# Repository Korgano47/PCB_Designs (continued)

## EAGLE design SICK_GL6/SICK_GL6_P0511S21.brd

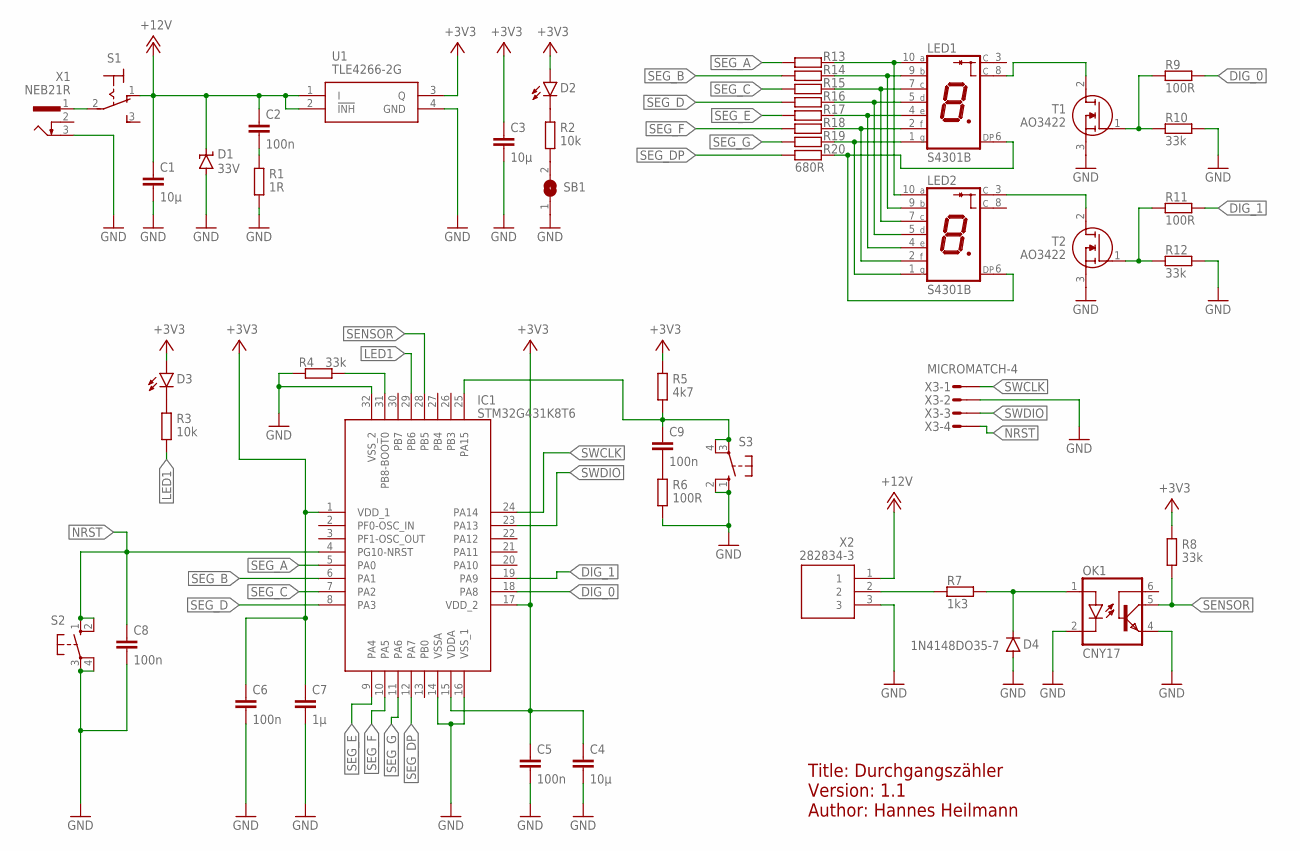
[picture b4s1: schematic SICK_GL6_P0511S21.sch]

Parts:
C1, C3, C4: 10µ; C1206K
C2, C5, C6, C8, C9: 100n; C0805K
C7: 1µ; C1206K
D1: 33V; SMBJ
D2, D3: LEDSML0805; SML0805
D4: 1N4148DO35-7; DO35-7
IC1: STM32G431K8T6; QFP80P900X900X160-32N
LED1, LED2: S4301B
OK1: CNY17; DIL06
R1: 1R; R0805
R2, R3: 10k; R0805
R4, R8, R10, R12: 33k; R0805
R5: 4k7; R0805
R6, R9, R11: 100R; R0805
R7: 1k3; R0805
R13, R14, R15, R16, R17, R18, R19, R20: 680R; R0805
S1: M9040P
S2, S3: 10-XX; B3F-10XX
SB1: SJ
T1, T2: AO3422; SOT95P237X112-3N
U1: TLE4266-2G; SOT230P700X170-4N
X1: NEB21R
X2: 282834-3; SHDR3W100P0X254_1X3_808X650X10
X3: MICROMATCH-4

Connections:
+3V3: C3.1, C4.1, C5.1, C6.1, C7.1, D2.A, D3.A, IC1.1 (VDD_1), IC1.15 (VDDA), IC1.17 (VDD_2), R5.2, R8.2, U1.3 (Q)
+12V: C1.1, C2.1, D1.C, S1.1 (O), U1.1 (I), U1.2 (!INH), X2.1
DIG_0: IC1.18 (PA8), R9.1
DIG_1: IC1.19 (PA9), R11.1
GND: C1.2, C3.2, C4.2, C5.2, C6.2, C7.2, C8.2, D1.A, D4.A, IC1.14 (VSSA), IC1.16 (VSS_1), IC1.32 (VSS_2), OK1.2 (C), OK1.4 (EMI), R1.1, R4.2, R6.1, R10.1, R12.1, S2.3, S2.4 (P1), S3.1 (S), S3.2 (S1), SB1.1, T1.3 (S), T2.3 (S), U1.4 (GND), X1.3, X2.3, X3.2
LED1: IC1.29 (PB6), R3.1
unnamed: S1.2, X1.1
unnamed: C2.2, R1.2
unnamed: D4.C, OK1.1 (A), R7.1
unnamed: LED2.3 (C), T2.2 (D)
unnamed: D2.C, R2.2
unnamed: R7.2, X2.2
unnamed: C9.1, IC1.25 (PA15), R5.1, S3.3, S3.4 (P1)
unnamed: C9.2, R6.2
unnamed: LED1.8 (C), T1.2 (D)
unnamed: IC1.31 (PB8-BOOT0), R4.1
unnamed: R2.1, SB1.2
unnamed: R11.2, R12.2, T2.1 (G)
unnamed: R9.2, R10.2, T1.1 (G)
unnamed: D3.C, R3.2
NRST: C8.1, IC1.4 (PG10-NRST), S2.1 (S), S2.2 (S1), X3.4
SEG_A: IC1.5 (PA0), R13.2
SEG_B: IC1.6 (PA1), R14.2
SEG_C: IC1.7 (PA2), R15.2
SEG_D: IC1.8 (PA3), R16.2
SEG_DP: IC1.12 (PA7), R20.2
SEG_E: IC1.9 (PA4), R17.2
SEG_F: IC1.10 (PA5), R18.2
SEG_G: IC1.11 (PA6), R19.2
SENSOR: IC1.28 (PB5), OK1.5 (COL), R8.1
SWCLK: IC1.24 (PA14), X3.1
SWDIO: IC1.23 (PA13), X3.3
S_A: LED1.10 (A), LED2.10 (A), R13.1
S_B: LED1.9 (B), LED2.9 (B), R14.1
S_C: LED1.7 (C), LED2.7 (C), R15.1
S_D: LED1.5 (D), LED2.5 (D), R16.1
S_DP: LED1.6 (DP), LED2.6 (DP), R20.1
S_E: LED1.4 (E), LED2.4 (E), R17.1
S_F: LED1.2 (F), LED2.2 (F), R18.1
S_G: LED1.1 (G), LED2.1 (G), R19.1

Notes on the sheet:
Title: Durchgangszähler Version: 1.1 Author: Hannes Heilmann

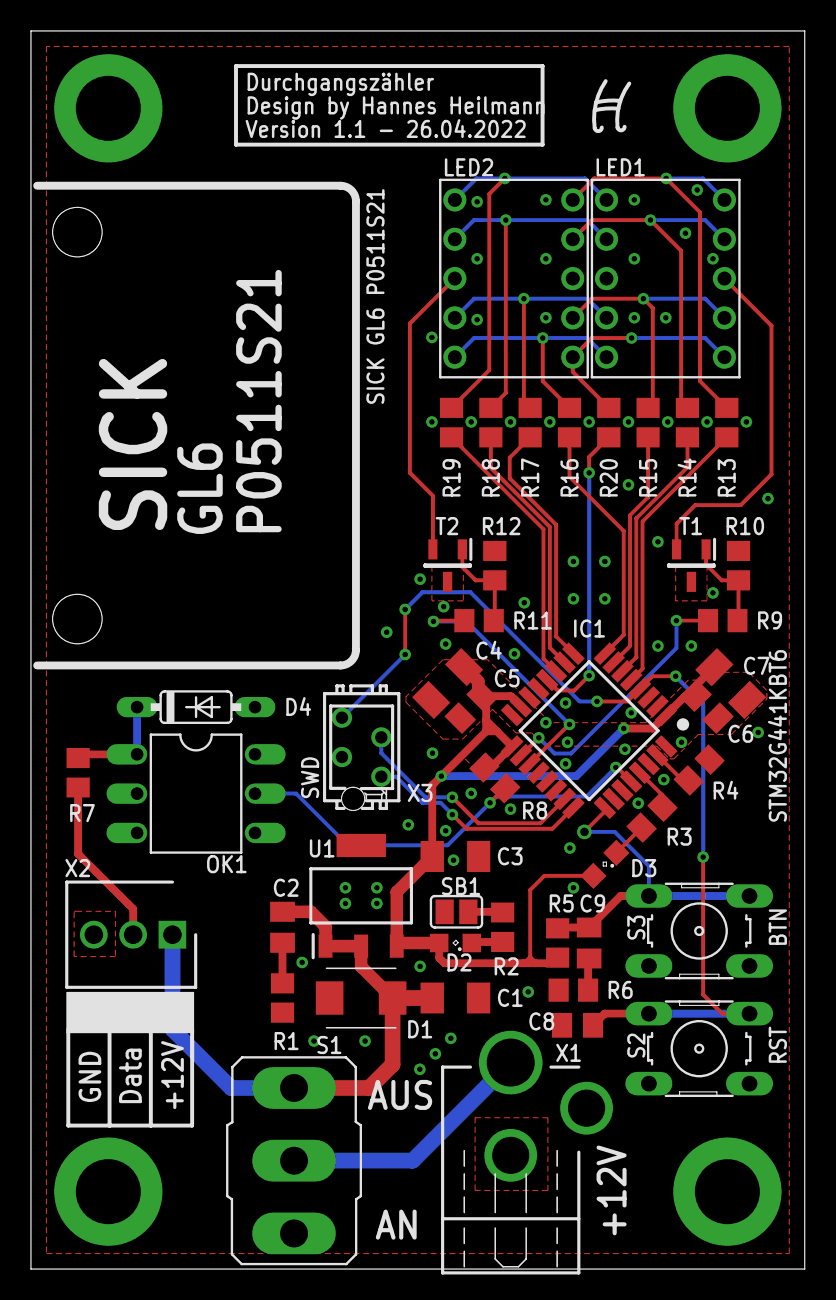
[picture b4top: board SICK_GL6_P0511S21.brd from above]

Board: 2 copper layers, 50.0 x 80.0 mm, 47 parts (0 on the bottom side), 40 nets.

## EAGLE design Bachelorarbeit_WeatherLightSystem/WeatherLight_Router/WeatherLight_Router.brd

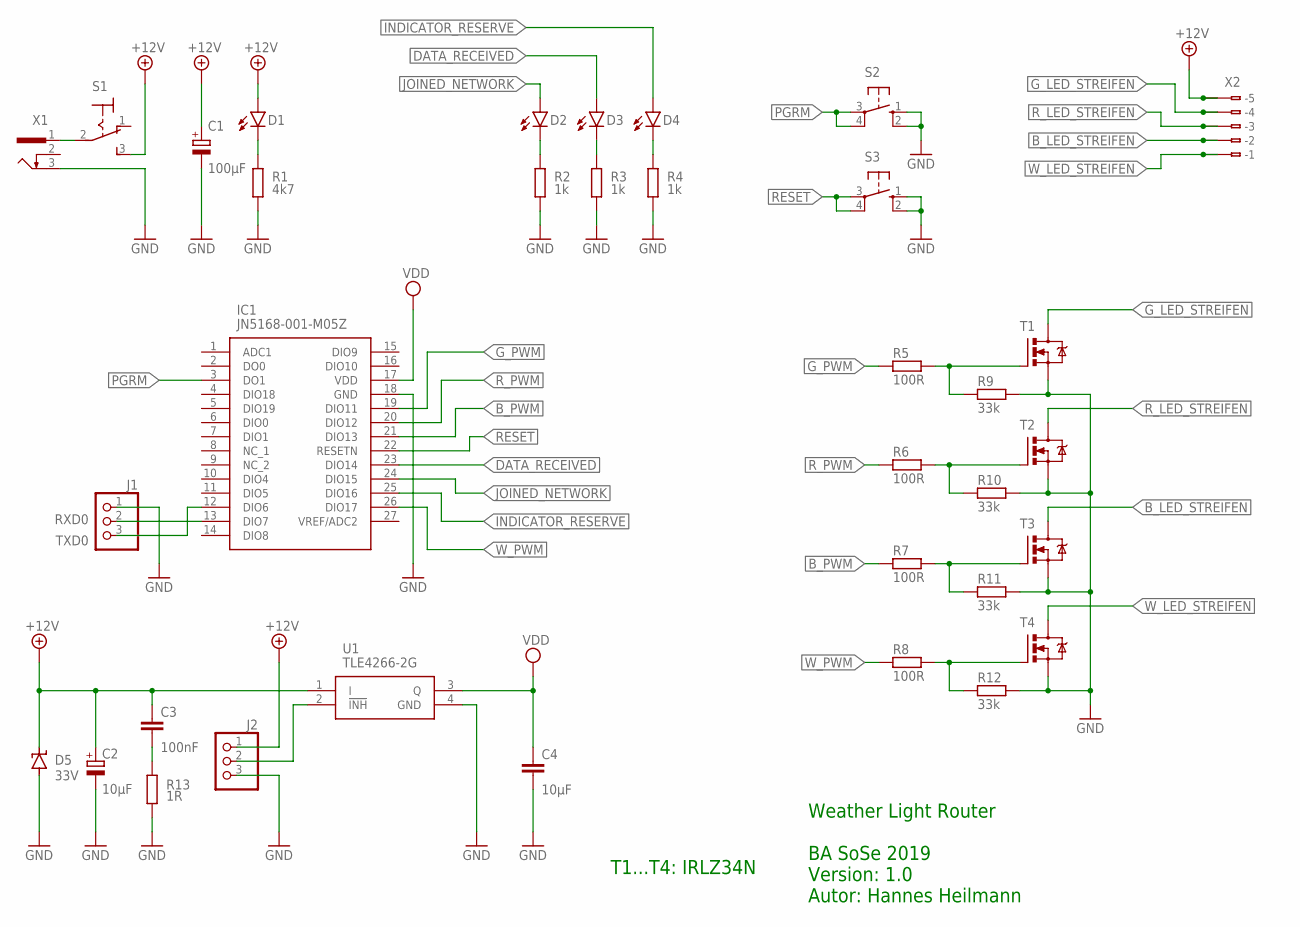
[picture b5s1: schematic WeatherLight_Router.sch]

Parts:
C1: 100µF; PANASONIC_D
C2: 10µF; PANASONIC_B
C3: 100nF; C1206
C4: 10µF; C1206K
D1, D2, D3, D4: LEDCHIPLED_1206; CHIPLED_1206
D5: 33V; SMBJ
IC1: JN5168-001-M05Z; JN5168001M05Z
J1, J2: PINHD-1X3; 1X03
R1: 4k7; R1206
R2, R3, R4: 1k; R1206
R5, R6, R7, R8: 100R; R1206
R9, R10, R11, R12: 33k; R1206
R13: 1R; R1206
S1: M9040P
S2, S3: 10-XX; B3F-10XX
T1, T2, T3, T4: IRLZ44Z; TO220BH
U1: TLE4266-2G; SOT230P700X170-4N
X1: NEB21R
X2: 233-505

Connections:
+12V: C1.+, C2.+, C3.1, D1.A, D5.C, J2.1, S1.3 (S), U1.1 (I), X2.A5 (-5), X2.B5 (B-5)
B_LED_STREIFEN: T3.D, X2.A2 (-2), X2.B2 (B-2)
B_PWM: IC1.21 (DIO13), R7.1
DATA_RECEIVED: D3.A, IC1.23 (DIO14)
GND: C1.-, C2.-, C4.2, D5.A, IC1.18 (GND), J1.1, J2.3, R1.1, R2.1, R3.1, R4.1, R9.2, R10.2, R11.2, R12.2, R13.1, S2.1 (S), S2.2 (S1), S3.1 (S), S3.2 (S1), T1.S, T2.S, T3.S, T4.S, U1.4 (GND), X1.3
G_LED_STREIFEN: T1.D, X2.A4 (-4), X2.B4 (B-4)
G_PWM: IC1.19 (DIO11), R5.1
INDICATOR_RESERVE: D4.A, IC1.25 (DIO16)
JOINED_NETWORK: D2.A, IC1.24 (DIO15)
unnamed: J2.2, U1.2 (!INH)
unnamed: S1.2, X1.1
unnamed: D1.C, R1.2
unnamed: D4.C, R4.2
unnamed: R7.2, R11.1, T3.G
unnamed: R8.2, R12.1, T4.G
unnamed: R6.2, R10.1, T2.G
unnamed: R5.2, R9.1, T1.G
unnamed: D3.C, R3.2
unnamed: D2.C, R2.2
unnamed: C3.2, R13.2
PGRM: IC1.3 (DO1), S2.3, S2.4 (P1)
RESET: IC1.22 (RESETN), S3.3, S3.4 (P1)
RXD0: IC1.13 (DIO7), J1.2
R_LED_STREIFEN: T2.D, X2.A3 (-3), X2.B3 (B-3)
R_PWM: IC1.20 (DIO12), R6.1
TXD0: IC1.12 (DIO6), J1.3
VDD: C4.1, IC1.17 (VDD), U1.3 (Q)
W_LED_STREIFEN: T4.D, X2.A1 (-1), X2.B1 (B-1)
W_PWM: IC1.26 (DIO17), R8.1

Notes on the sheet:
Weather Light Router BA SoSe 2019 Version: 1.0 Autor: Hannes Heilmann
T1...T4: IRLZ34N

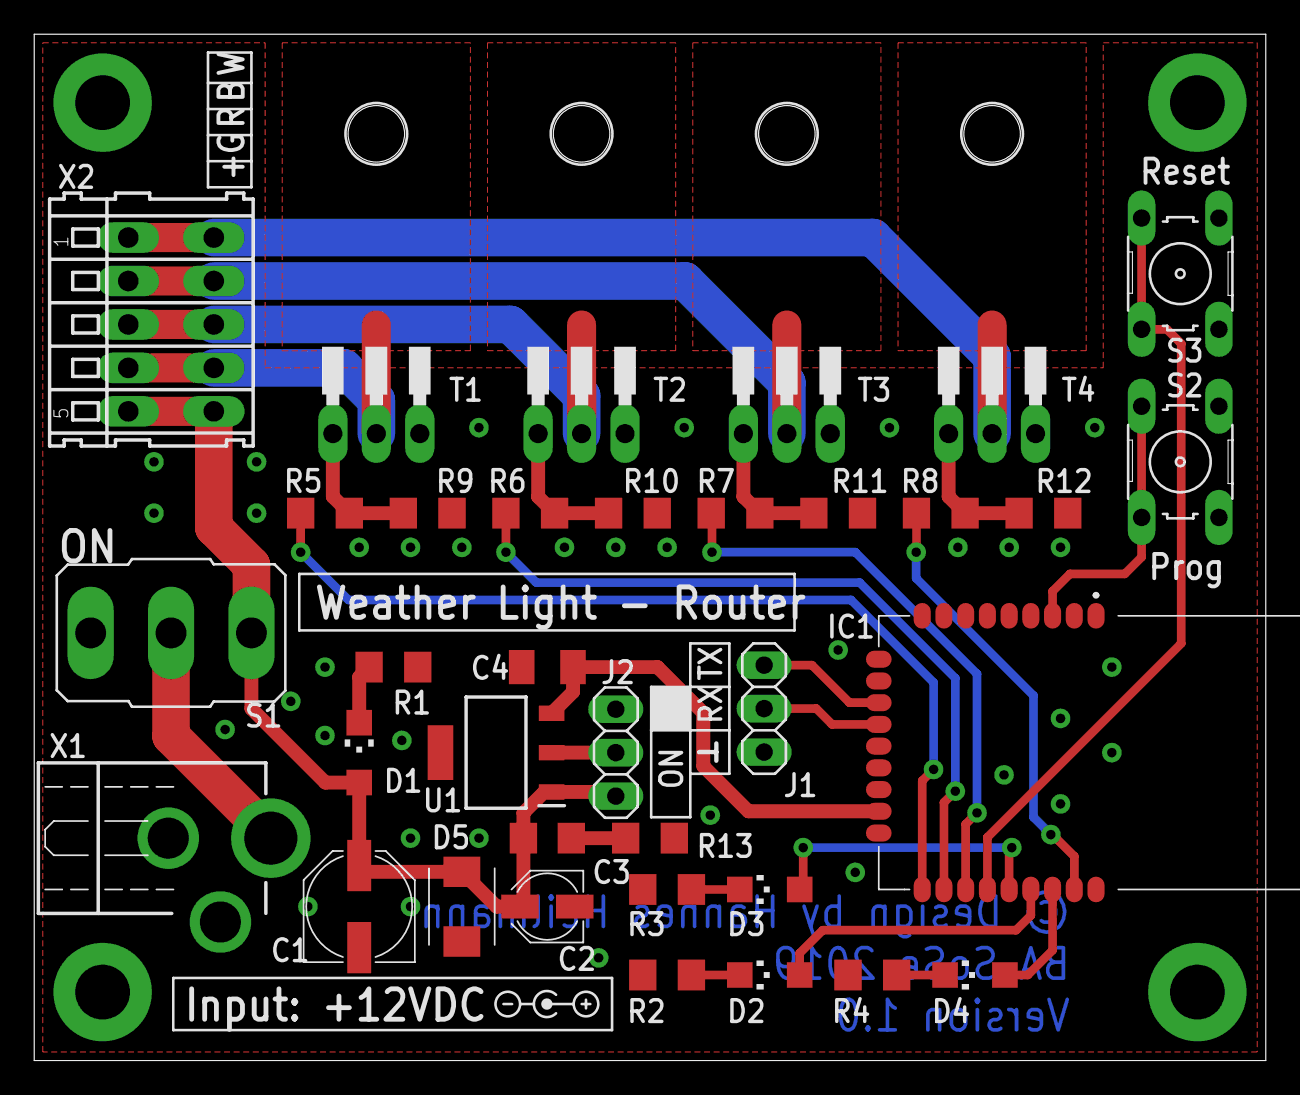
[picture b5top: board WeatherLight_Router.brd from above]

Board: 2 copper layers, 72.0 x 60.0 mm, 35 parts (0 on the bottom side), 29 nets.

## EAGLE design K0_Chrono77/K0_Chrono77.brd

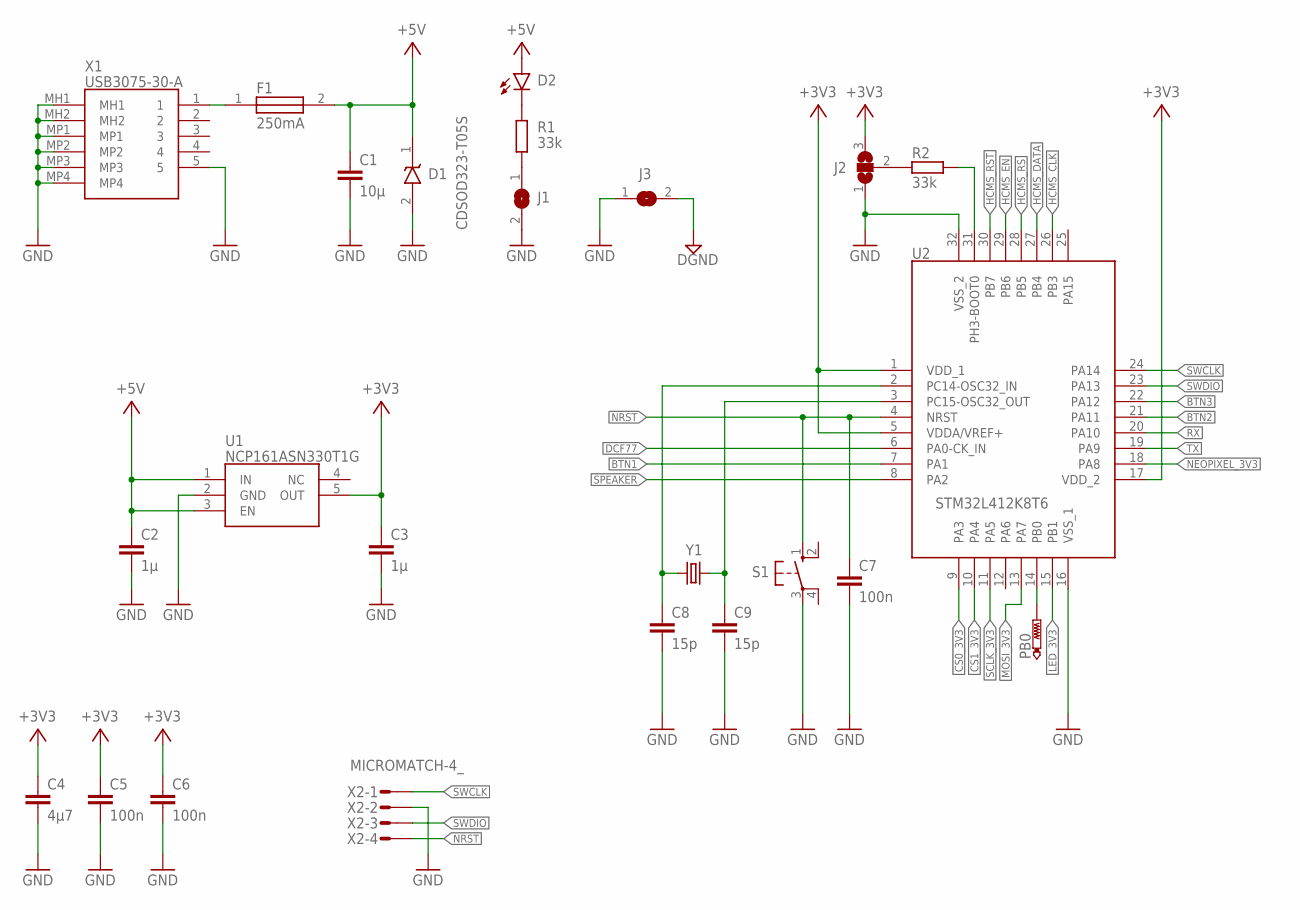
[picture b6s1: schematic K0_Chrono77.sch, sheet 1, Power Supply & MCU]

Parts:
C1: 10μ; C1206
C2, C3: 1μ; C0805
C4: 4μ7; C0805
C5, C6, C7: 100n; C0805
C8, C9: 15p; C0805
D1: CDSOD323-T05S; SOD2513X114N
D2: LED_0805; CHIP-LED0805
F1: SF-2410FP150T-2; VARC6126X270N
J1, J3: SJ
J2: SJ2W; SJ_2
PB0: PTR1TP14R; TP14R
R1, R2: 33k; R0805
S1: 10-XX; B3F-10XX
U1: NCP161ASN330T1G; SOT95P280X145-5N
U2: STM32L412K8T6; QFP80P900X900X160-32N
X1: USB3075-30-A; USB307530A
X2: MICROMATCH-4_; MICROMATCH-4
Y1: CRYSTALTC26H; TC26H

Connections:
+3V3: C3.1, C4.1, C5.1, C6.1, J2.3, U1.5 (OUT), U2.1 (VDD_1), U2.5 (VDDA/VREF+), U2.17 (VDD_2); also elsewhere on the board
+5V: C1.1, C2.1, D1.1 (K), D2.A, F1.2, U1.1 (IN), U1.3 (EN); also elsewhere on the board
BTN1: U2.7 (PA1); also elsewhere on the board
BTN2: U2.21 (PA11); also elsewhere on the board
BTN3: U2.22 (PA12); also elsewhere on the board
CS0_3V3: U2.9 (PA3); also elsewhere on the board
CS1_3V3: U2.10 (PA4); also elsewhere on the board
DCF77: U2.6 (PA0-CK_IN); also elsewhere on the board
DGND: J3.2; also elsewhere on the board
GND: C1.2, C2.2, C3.2, C4.2, C5.2, C6.2, C7.2, C8.2, C9.2, D1.2 (A), J1.2, J2.1, J3.1, S1.3, U1.2 (GND), U2.16 (VSS_1), U2.32 (VSS_2), X1.5, X1.MH1, X1.MH2, X1.MP1, X1.MP2, X1.MP3, X1.MP4, X2.2; also elsewhere on the board
HCMS_CLK: U2.26 (PB3); also elsewhere on the board
HCMS_DATA: U2.27 (PB4); also elsewhere on the board
HCMS_EN: U2.29 (PB6); also elsewhere on the board
HCMS_RS: U2.28 (PB5); also elsewhere on the board
HCMS_RST: U2.30 (PB7); also elsewhere on the board
LED_3V3: U2.15 (PB1); also elsewhere on the board
MOSI_3V3: U2.13 (PA7); also elsewhere on the board
unnamed: F1.1, X1.1
unnamed: D2.C, R1.2
unnamed: J1.1, R1.1
unnamed: R2.2, U2.31 (PH3-BOOT0)
unnamed: J2.2, R2.1
unnamed: PB0.TP, U2.14 (PB0)
NEOPIXEL_3V3: U2.18 (PA8); also elsewhere on the board
NRST: C7.1, S1.1 (S), U2.4 (NRST), X2.4
OSC32_IN: C8.1, U2.2 (PC14-OSC32_IN), Y1.2
OSC32_OUT: C9.1, U2.3 (PC15-OSC32_OUT), Y1.1
RX: U2.20 (PA10); also elsewhere on the board
SCLK_3V3: U2.11 (PA5); also elsewhere on the board
SPEAKER: U2.8 (PA2); also elsewhere on the board
SWCLK: U2.24 (PA14), X2.1
SWDIO: U2.23 (PA13), X2.3
TX: U2.19 (PA9); also elsewhere on the board

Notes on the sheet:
250mA

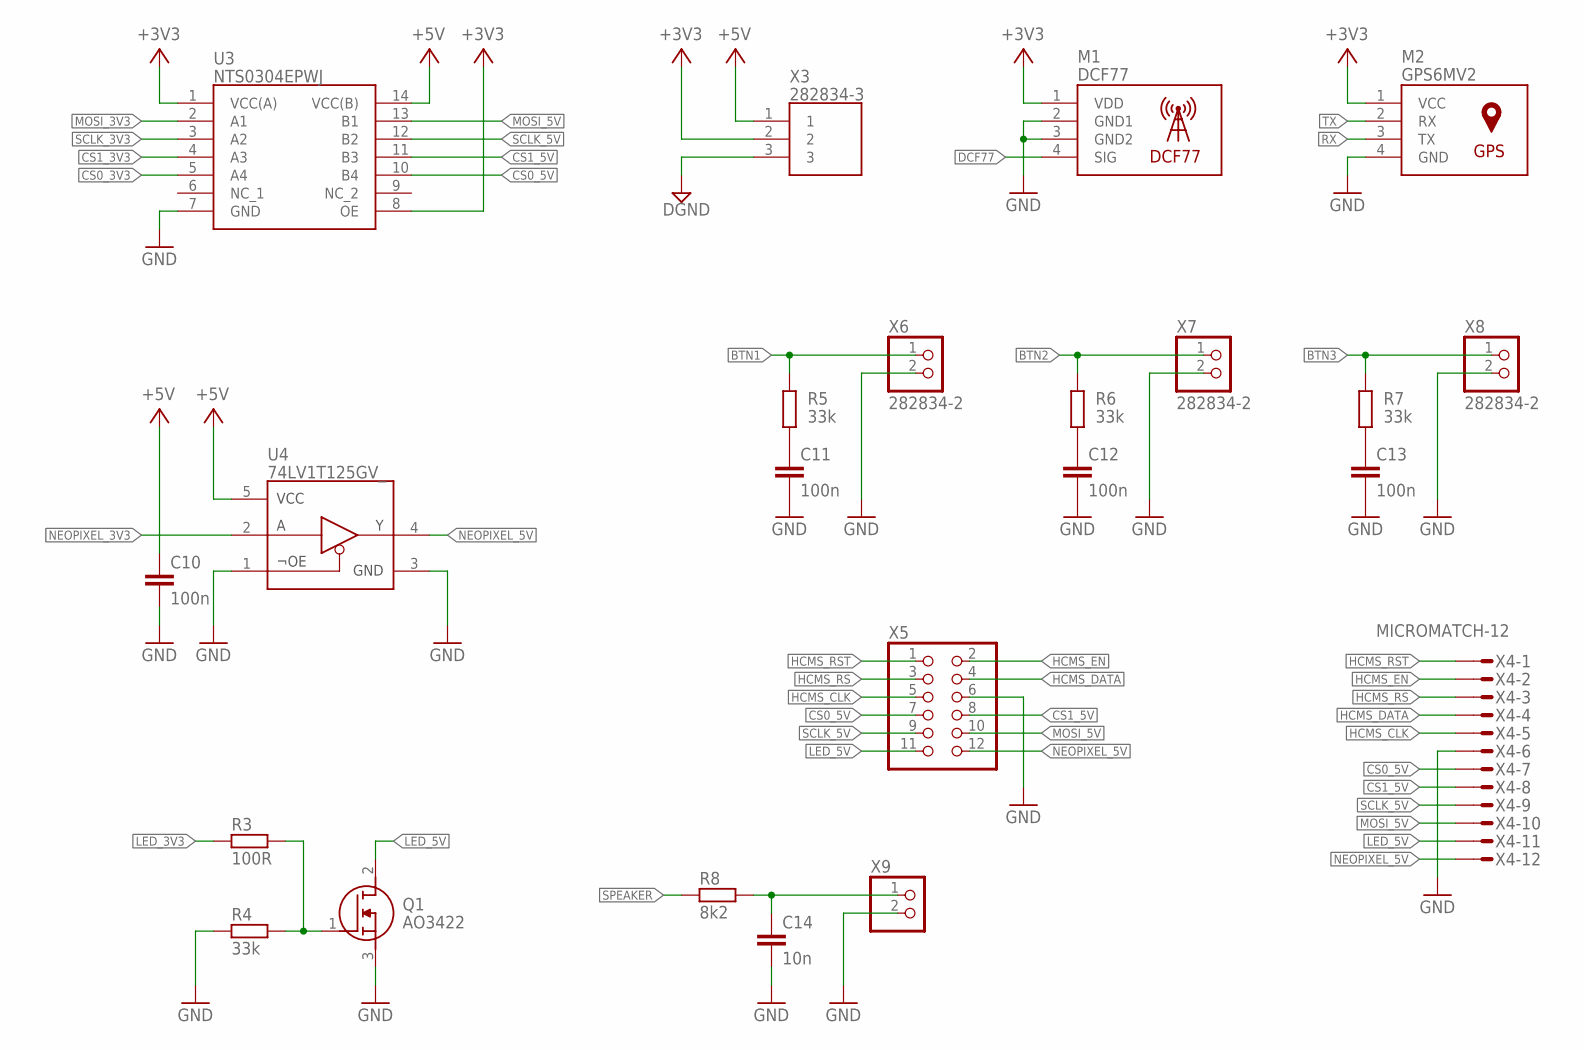
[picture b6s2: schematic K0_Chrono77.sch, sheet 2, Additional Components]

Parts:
C10, C11, C12, C13: 100n; C0805
C14: 10n; C0805
M1: DCF77
M2: GPS6MV2
Q1: AO3422; SOT95P237X112-3N
R3: 100R; R0805
R4, R5, R6, R7: 33k; R0805
R8: 8k2; R0805
U3: NTS0304EPWJ; SOP65P640X110-14N
U4: 74LV1T125GV_; SOT753
X3: 282834-3; SHDR3W100P0X254_1X3_808X650X10
X4: MICROMATCH-12
X5: PINHD-2X6; 2X06
X6, X7, X8: 282834-2; SHDR2W85P0X254_1X2_554X650X103
X9: PINHD-1X2/90; 1X02/90

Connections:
+3V3: M1.1 (VDD), M2.1 (VCC), U3.1 (VCC(A)), U3.8 (OE), X3.2; also elsewhere on the board
+5V: C10.1, U3.14 (VCC(B)), U4.5 (VCC), X3.1; also elsewhere on the board
BTN1: R5.2, X6.1; also elsewhere on the board
BTN2: R6.2, X7.1; also elsewhere on the board
BTN3: R7.2, X8.1; also elsewhere on the board
CS0_3V3: U3.5 (A4); also elsewhere on the board
CS0_5V: U3.10 (B4), X4.7, X5.7
CS1_3V3: U3.4 (A3); also elsewhere on the board
CS1_5V: U3.11 (B3), X4.8, X5.8
DCF77: M1.4 (SIG); also elsewhere on the board
DGND: X3.3; also elsewhere on the board
GND: C10.2, C11.2, C12.2, C13.2, C14.2, M1.2 (GND1), M1.3 (GND2), M2.4 (GND), Q1.3 (S), R4.1, U3.7 (GND), U4.1 (¬OE), U4.3 (GND), X4.6, X5.6, X6.2, X7.2, X8.2, X9.2; also elsewhere on the board
HCMS_CLK: X4.5, X5.5; also elsewhere on the board
HCMS_DATA: X4.4, X5.4; also elsewhere on the board
HCMS_EN: X4.2, X5.2; also elsewhere on the board
HCMS_RS: X4.3, X5.3; also elsewhere on the board
HCMS_RST: X4.1, X5.1; also elsewhere on the board
LED_3V3: R3.1; also elsewhere on the board
LED_5V: Q1.2 (D), X4.11, X5.11
MOSI_3V3: U3.2 (A1); also elsewhere on the board
MOSI_5V: U3.13 (B1), X4.10, X5.10
unnamed: C11.1, R5.1
unnamed: C12.1, R6.1
unnamed: Q1.1 (G), R3.2, R4.2
unnamed: C13.1, R7.1
unnamed: C14.1, R8.2, X9.1
NEOPIXEL_3V3: U4.2 (A); also elsewhere on the board
NEOPIXEL_5V: U4.4 (Y), X4.12, X5.12
RX: M2.3 (TX); also elsewhere on the board
SCLK_3V3: U3.3 (A2); also elsewhere on the board
SCLK_5V: U3.12 (B2), X4.9, X5.9
SPEAKER: R8.1; also elsewhere on the board
TX: M2.2 (RX); also elsewhere on the board

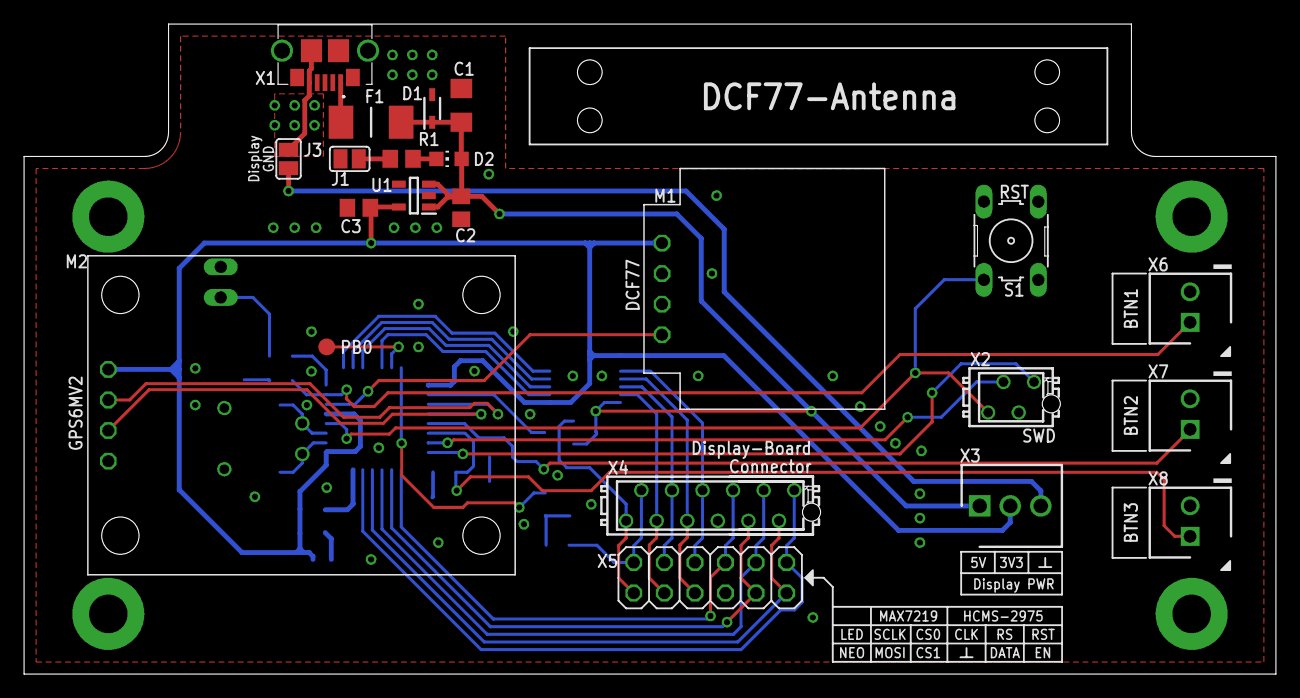
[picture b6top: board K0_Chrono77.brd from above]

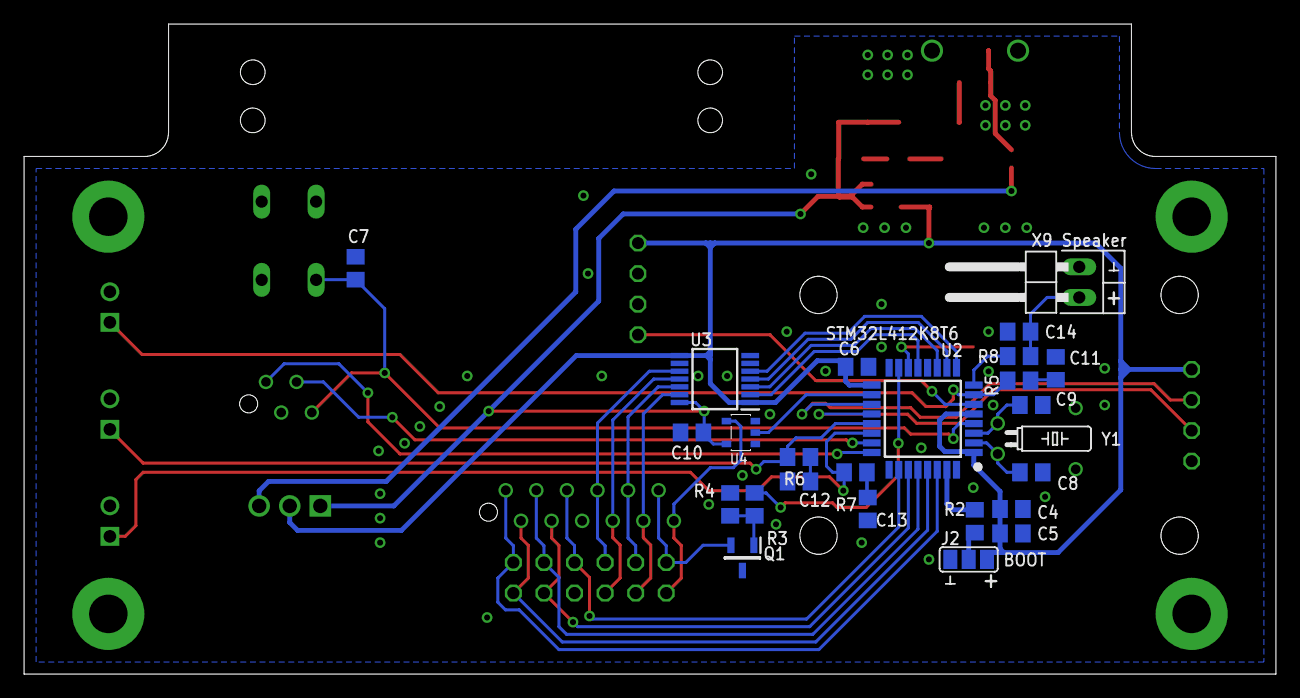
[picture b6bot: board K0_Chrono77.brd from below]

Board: 2 copper layers, 104.0 x 54.0 mm, 47 parts (25 on the bottom side), 44 nets.

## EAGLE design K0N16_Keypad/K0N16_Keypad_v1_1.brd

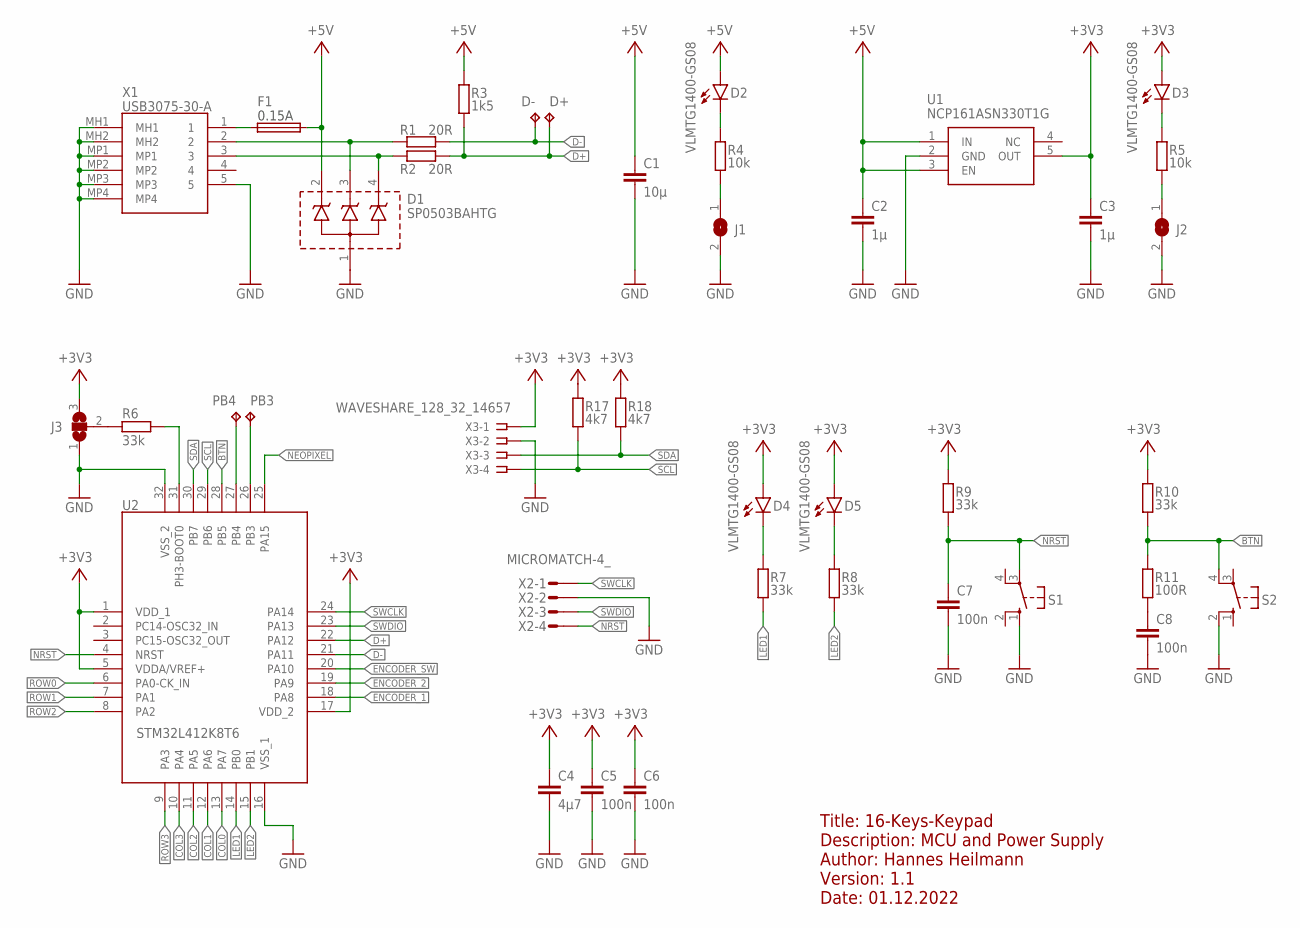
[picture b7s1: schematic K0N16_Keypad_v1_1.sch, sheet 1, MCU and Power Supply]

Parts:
C1: 10μ; C1206
C2, C3: 1μ; C0805
C4: 4μ7; C0805
C5, C6, C7, C8: 100n; C0805
D1: SP0503BAHTG
D2, D3, D4, D5: VLMTG1400-GS08; CHIP-LED0805
D+: TPB1,27; B1,27
D-: TPB1,27; B1,27
F1: FUSE_0603R0603; R0603
J1, J2: SJ
J3: SJ2W; SJ_2
PB3, PB4: TPB1,27; B1,27
R1, R2: 20R; R0805
R3: 1k5; R0805
R4, R5: 10k; R0805
R6, R7, R8, R9, R10: 33k; R0805
R11: 100R; R0805
R17, R18: 4k7; R0805
S1, S2: 10-XXB3F_10XX; B3F-10XX
U1: NCP161ASN330T1G; SOT95P280X145-5N
U2: STM32L412K8T6; QFP80P900X900X160-32N
X1: USB3075-30-A; USB307530A
X2: MICROMATCH-4_; MICROMATCH-4
X3: WAVESHARE_128_32_14657; SSW-104-02-G-S

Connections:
+3V3: C3.1, C4.1, C5.1, C6.1, D3.A, D4.A, D5.A, J3.3, R9.1, R10.1, R17.1, R18.1, U1.5 (OUT), U2.1 (VDD_1), U2.5 (VDDA/VREF+), U2.17 (VDD_2), X3.1; also elsewhere on the board
+5V: C1.1, C2.1, D1.2 (K_1), D2.A, F1.2, R3.2, U1.1 (IN), U1.3 (EN); also elsewhere on the board
BOOT0: R6.1, U2.31 (PH3-BOOT0)
BTN: R10.2, R11.1, S2.4 (P1), U2.28 (PB5)
COL0: U2.13 (PA7); also elsewhere on the board
COL1: U2.12 (PA6); also elsewhere on the board
COL2: U2.11 (PA5); also elsewhere on the board
COL3: U2.10 (PA4); also elsewhere on the board
D+: D+.TP, R2.2, R3.1, U2.22 (PA12)
D-: D-.TP, R1.2, U2.21 (PA11)
ENCODER_1: U2.18 (PA8); also elsewhere on the board
ENCODER_2: U2.19 (PA9); also elsewhere on the board
ENCODER_SW: U2.20 (PA10); also elsewhere on the board
GND: C1.2, C2.2, C3.2, C4.2, C5.2, C6.2, C7.2, C8.2, D1.1 (COMMON_A), J1.2, J2.2, J3.1, S1.1 (S), S2.2 (S1), U1.2 (GND), U2.16 (VSS_1), U2.32 (VSS_2), X1.5, X1.MH1, X1.MH2, X1.MP1, X1.MP2, X1.MP3, X1.MP4, X2.2, X3.2; also elsewhere on the board
LED1: R7.2, U2.14 (PB0)
LED2: R8.2, U2.15 (PB1)
unnamed: D1.3 (K_2), R1.1, X1.2
unnamed: D1.4 (K_3), R2.1, X1.3
unnamed: D2.C, R4.2
unnamed: J1.1, R4.1
unnamed: J2.1, R5.1
unnamed: D3.C, R5.2
unnamed: J3.2, R6.2
unnamed: PB4.TP, U2.27 (PB4)
unnamed: PB3.TP, U2.26 (PB3)
unnamed: F1.1, X1.1
unnamed: C8.1, R11.2
unnamed: D4.C, R7.1
unnamed: D5.C, R8.1
NEOPIXEL: U2.25 (PA15); also elsewhere on the board
NRST: C7.1, R9.2, S1.3, U2.4 (NRST), X2.4
ROW0: U2.6 (PA0-CK_IN); also elsewhere on the board
ROW1: U2.7 (PA1); also elsewhere on the board
ROW2: U2.8 (PA2); also elsewhere on the board
ROW3: U2.9 (PA3); also elsewhere on the board
SCL: R17.2, U2.29 (PB6), X3.4
SDA: R18.2, U2.30 (PB7), X3.3
SWCLK: U2.24 (PA14), X2.1
SWDIO: U2.23 (PA13), X2.3

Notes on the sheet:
0.15A
Title: 16-Keys-Keypad Description: MCU and Power Supply Author: Hannes Heilmann Version: 1.1 Date: 01.12.2022

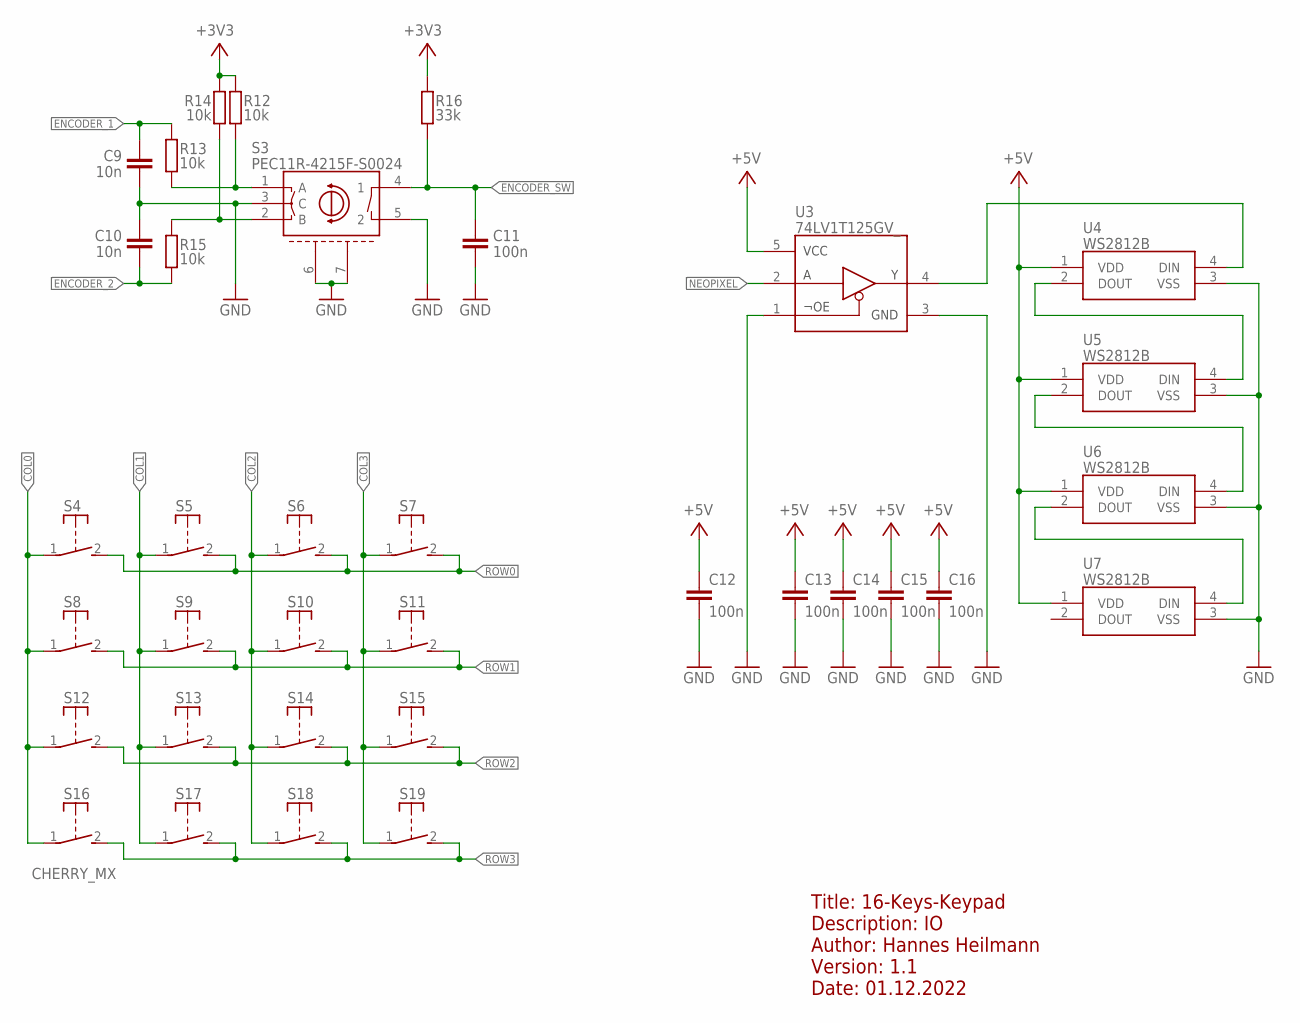
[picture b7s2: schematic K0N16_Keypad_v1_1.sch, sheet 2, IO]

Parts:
C9, C10: 10n; C0805
C11, C12, C13, C14, C15, C16: 100n; C0805
R12, R13, R14, R15: 10k; R0805
R16: 33k; R0805
S3: PEC11R-4215F-S0024; PEC12R-4XXXF-SXXXX_1
S4, S5, S6, S7, S8, S9, S10, S11, S12, S13, S14, S15, S16, S17, S18, S19: CHERRY_MX
U3: 74LV1T125GV_; SOT753
U4, U5, U6, U7: WS2812B

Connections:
+3V3: R12.1, R14.1, R16.1; also elsewhere on the board
+5V: C12.1, C13.1, C14.1, C15.1, C16.1, U3.5 (VCC), U4.1 (VDD), U5.1 (VDD), U6.1 (VDD), U7.1 (VDD); also elsewhere on the board
COL0: S4.1, S8.1, S12.1, S16.1; also elsewhere on the board
COL1: S5.1, S9.1, S13.1, S17.1; also elsewhere on the board
COL2: S6.1, S10.1, S14.1, S18.1; also elsewhere on the board
COL3: S7.1, S11.1, S15.1, S19.1; also elsewhere on the board
ENCODER_1: C9.1, R13.2; also elsewhere on the board
ENCODER_2: C10.2, R15.2; also elsewhere on the board
ENCODER_SW: C11.1, R16.2, S3.4 (1); also elsewhere on the board
GND: C9.2, C10.1, C11.2, C12.2, C13.2, C14.2, C15.2, C16.2, S3.3 (C), S3.5 (2), S3.6 (GND1), S3.7 (GND2), U3.1 (¬OE), U3.3 (GND), U4.3 (VSS), U5.3 (VSS), U6.3 (VSS), U7.3 (VSS); also elsewhere on the board
unnamed: R12.2, R13.1, S3.1 (A)
unnamed: R14.2, R15.1, S3.2 (B)
unnamed: U4.2 (DOUT), U5.4 (DIN)
unnamed: U5.2 (DOUT), U6.4 (DIN)
unnamed: U6.2 (DOUT), U7.4 (DIN)
unnamed: U3.4 (Y), U4.4 (DIN)
NEOPIXEL: U3.2 (A); also elsewhere on the board
ROW0: S4.2 (S), S5.2 (S), S6.2 (S), S7.2 (S); also elsewhere on the board
ROW1: S8.2 (S), S9.2 (S), S10.2 (S), S11.2 (S); also elsewhere on the board
ROW2: S12.2 (S), S13.2 (S), S14.2 (S), S15.2 (S); also elsewhere on the board
ROW3: S16.2 (S), S17.2 (S), S18.2 (S), S19.2 (S); also elsewhere on the board

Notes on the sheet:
Title: 16-Keys-Keypad Description: IO Author: Hannes Heilmann Version: 1.1 Date: 01.12.2022

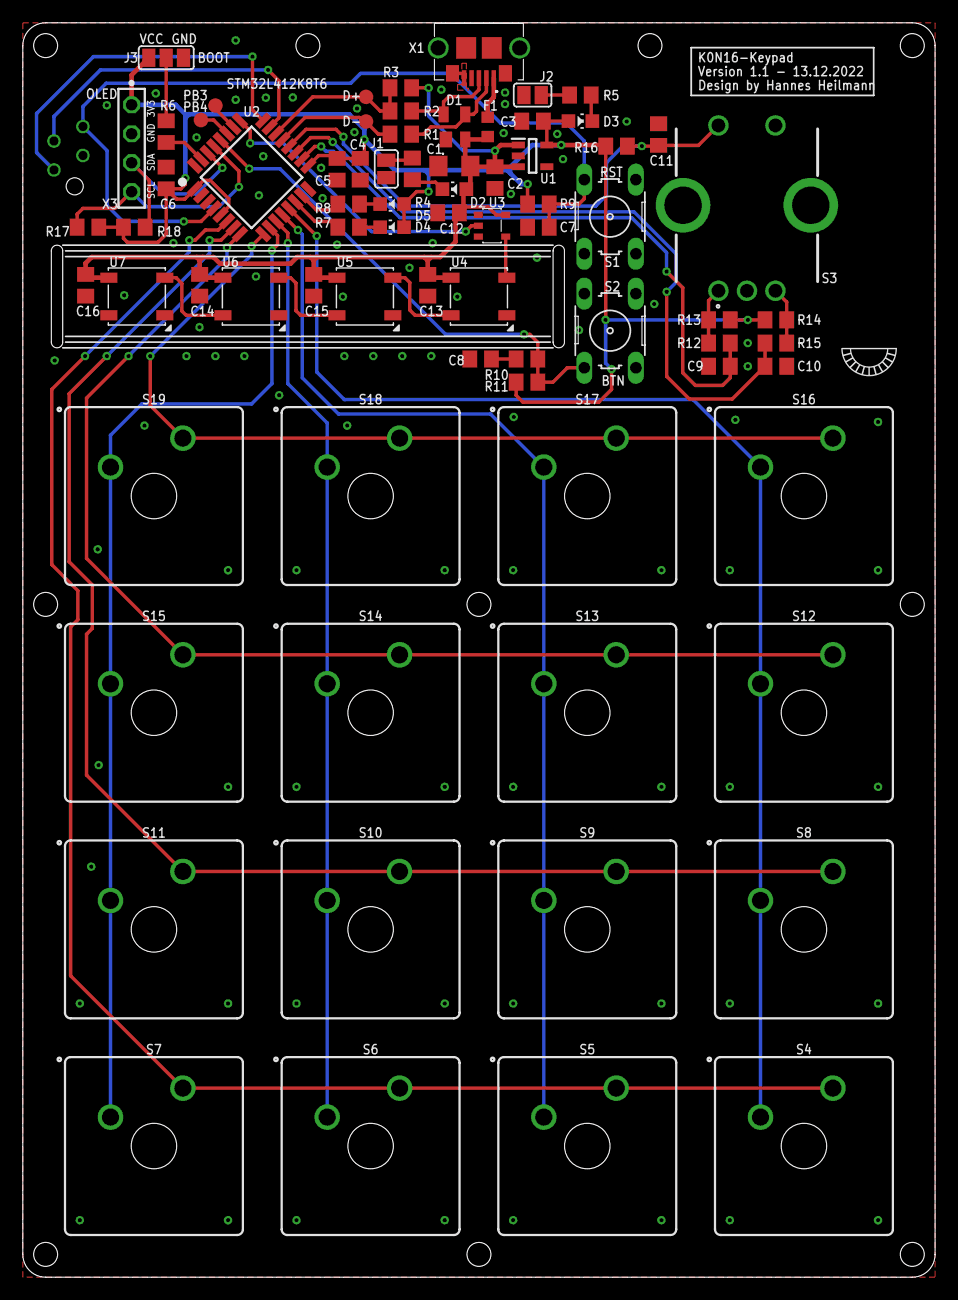
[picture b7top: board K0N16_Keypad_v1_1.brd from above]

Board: 2 copper layers, 80.0 x 110.0 mm, 76 parts (1 on the bottom side), 45 nets.

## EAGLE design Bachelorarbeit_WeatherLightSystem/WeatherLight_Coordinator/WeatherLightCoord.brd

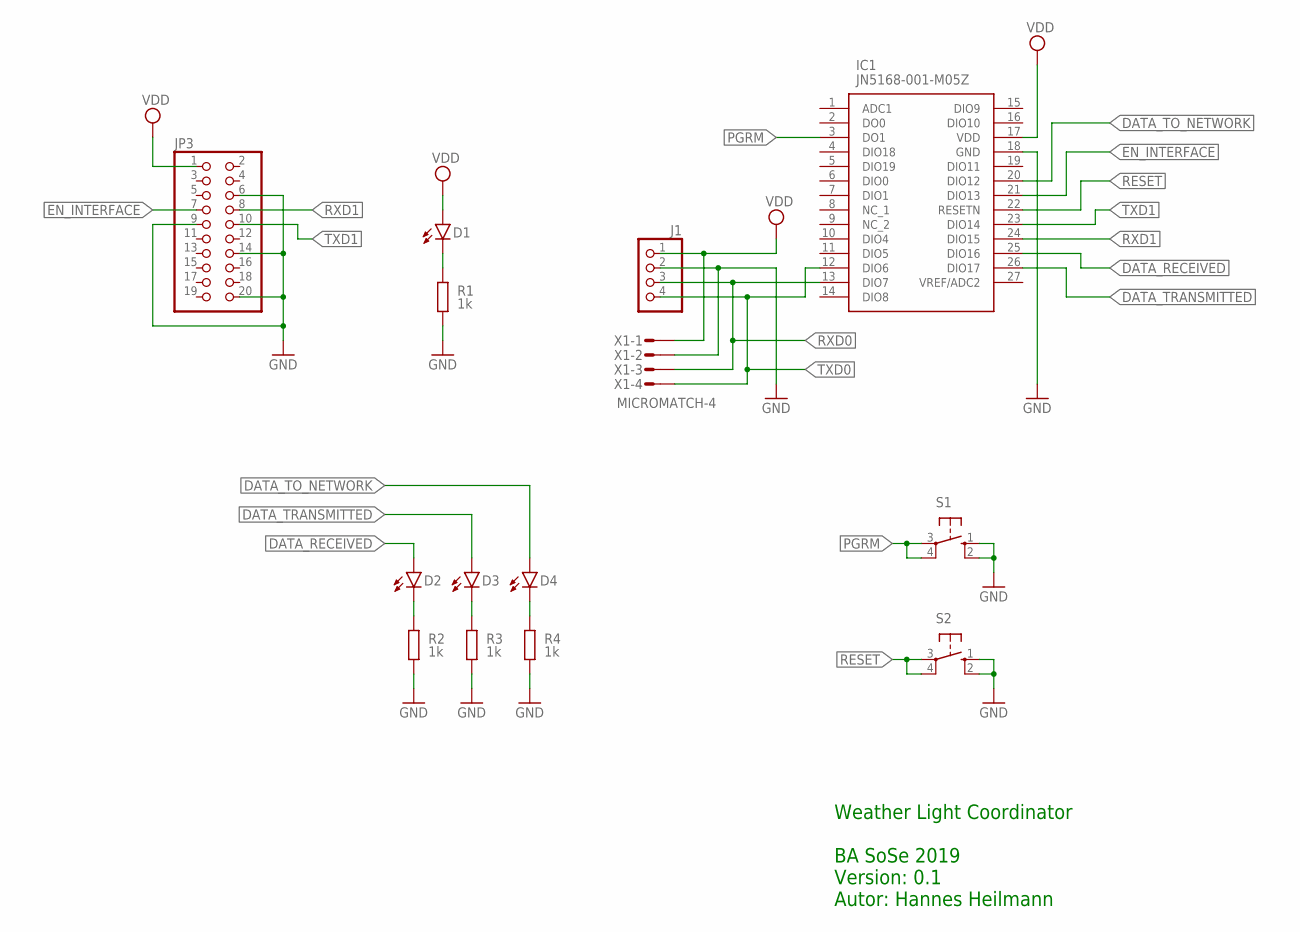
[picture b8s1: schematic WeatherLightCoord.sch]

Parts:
D1, D2, D3, D4: LEDCHIPLED_1206; CHIPLED_1206
IC1: JN5168-001-M05Z; JN5168001M05Z
J1: PINHD-1X4; 1X04
JP3: PINHD-2X10; 2X10
R1, R2, R3, R4: 1k; R1206
S1, S2: 10-XX; B3F-10XX
X1: MICROMATCH-4

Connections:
DATA_RECEIVED: D2.A, IC1.25 (DIO16)
DATA_TO_NETWORK: D4.A, IC1.20 (DIO12)
DATA_TRANSMITTED: D3.A, IC1.26 (DIO17)
EN_INTERFACE: IC1.21 (DIO13), JP3.7
GND: IC1.18 (GND), J1.2, JP3.6, JP3.9, JP3.14, JP3.20, R1.1, R2.1, R3.1, R4.1, S1.1 (S), S1.2 (S1), S2.1 (S), S2.2 (S1), X1.2
unnamed: D1.C, R1.2
unnamed: D4.C, R4.2
unnamed: D3.C, R3.2
unnamed: D2.C, R2.2
PGRM: IC1.3 (DO1), S1.3, S1.4 (P1)
RESET: IC1.22 (RESETN), S2.3, S2.4 (P1)
RXD0: IC1.13 (DIO7), J1.3, X1.3
RXD1: IC1.24 (DIO15), JP3.8
TXD0: IC1.12 (DIO6), J1.4, X1.4
TXD1: IC1.23 (DIO14), JP3.10
VDD: D1.A, IC1.17 (VDD), J1.1, JP3.1, X1.1

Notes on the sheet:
Weather Light Coordinator BA SoSe 2019 Version: 0.1 Autor: Hannes Heilmann
